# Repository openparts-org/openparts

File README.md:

# openparts

OpenParts -- an open, provenance-tracked data platform for electronic
components that generates reproducible EDA/MCAD assets from Canonical
Data instead of distributing pre-made CAD files. This repository holds
all of its code: the core libraries, validators, generators and CLI
(`crates/`), the distribution API server (`server/`), the web site
(`web/`) and the KiCad plugin (`kicad-plugin/`).

See [`docs/spec/`](docs/spec/) for the full specification set. Component
data lives in the `openparts-data` repository, checked out next to this
one (`../openparts-data`): tests, `openparts validate --data` and the
server read it from there.

## Status

First Vertical Slice (Architecture Specification section 32):
Canonical YAML -> Parser -> Validator -> Effective Model -> KiCad + STEP.
Package support covers the LQFP/TQFP, QFN, SOIC, TSSOP, SSOP, MSOP/VSSOP,
SOT, SOT-223, TO-252 (DPAK), chip (2-terminal), radial, axial, TO-92, DIP,
SIP and BGA families, castellated modules (`module`, e.g. Raspberry Pi
Pico), straight through-hole pin headers and socket strips (`header`,
`socket`; 1 or 2 rows), shrouded wire-to-board headers with an
off-centre housing (`shrouded_header`, e.g. JST XH/PH) and right-angle
pin headers (`right_angle_header`, 1 row).

3D models (STEP, STL, coloured 3MF, and an editable SolidCraft design)
are built by `openparts-solidcraft` and exported by a locally installed
[SolidCraft](https://solidcraft.io) -- see "3D models" below.

The CLI has `generate`, `validate`, `search`, `show` and `bundle` --
see "Prebuilt artifacts" below for `bundle`.

## Layout

```text
server/                  openparts-server: REST API + bundled artifacts
web/                     openparts-web: the MoonBit (rabbita) site (api/types.mbt is
                         generated from the Rust types: web/scripts/gen-api-types.sh)
kicad-plugin/            KiCad plugin (library sync GUI + launcher)
deploy/raspberry-pi/     deploy the server on a Raspberry Pi behind a Cloudflare Tunnel
crates/
├── openparts-artifacts  Part -> every artifact; the bundle manifest schema
├── openparts-core        Canonical Rust data model
├── openparts-data         YAML <-> core model
├── openparts-validator     cross-entity validation
├── openparts-client        API client for openparts-server
├── openparts-cli           command-line interface
├── pcbcad/
│   ├── openparts-pcbcad    PCB CAD-independent Symbol/Footprint IR
│   ├── openparts-kicad      KiCad adapter
│   ├── openparts-librepcb   LibrePCB adapter
│   └── openparts-pcbcraft   PCBCraft native library adapter
└── mcad/
    ├── openparts-mcad       Mechanical Geometry generators
    ├── openparts-solidcraft Mechanical Geometry -> detailed parametric
    │                        SolidCraft model, run through SolidCraft
    ├── openparts-step       STEP exporter (via openparts-solidcraft)
    └── openparts-stl        binary STL exporter (via openparts-solidcraft)
```

## Usage

```sh
cargo build --workspace
cargo test --workspace

cargo run -p openparts-cli -- validate \
  --part   ../openparts-data/parts/exemplar/ex48/EX48F100Q6.yaml \
  --device ../openparts-data/devices/exemplar/EX48F100.yaml \
  --package ../openparts-data/packages/standards/lqfp/LQFP48-7x7-P0.5.yaml \
  --source ../openparts-data/sources/exemplar/EX-DS-0001.yaml

cargo run -p openparts-cli -- generate \
  --part   ../openparts-data/parts/exemplar/ex48/EX48F100Q6.yaml \
  --device ../openparts-data/devices/exemplar/EX48F100.yaml \
  --package ../openparts-data/packages/standards/lqfp/LQFP48-7x7-P0.5.yaml \
  --source ../openparts-data/sources/exemplar/EX-DS-0001.yaml \
  --out /tmp/openparts-out
```

`generate` writes the KiCad symbol/footprint, STEP, STL, 3MF, the
SolidCraft design (`.sc`), a LibrePCB library and a generation report
for one part.

## Prebuilt artifacts

`bundle` builds every part of an `openparts-data` checkout at once, for
shipping to `openparts-server` (which then needs no SolidCraft):

```sh
cargo run --release -p openparts-cli -- bundle \
  --data ../openparts-data --out /tmp/openparts-bundle [--jobs N] [--strict]
```

Each part is validated, its Effective Model built for the base silicon
revision, and its artifacts written content-addressed (Architecture
Specification section 24) -- SolidCraft runs once per part for all 3D
formats, parts in parallel (`--jobs`, default: CPU count):

```text
<out>/
├── manifest.json
└── artifacts/sha256/<hex>     STEP, binary STL, 3MF, .sc design,
                               .kicad_sym, .kicad_mod
```

`manifest.json` (`"format": "openparts-bundle"`, `"format_version": 1`):

- `artifact_path`: `"artifacts/sha256/{sha256}"`.
- `reproducibility`: dataset git commit (and whether it was dirty),
  `schema_versions`, generator crate versions and the openparts source
  commit, `toolchain` (SolidCraft and rustc versions),
  `silicon_revision` (`null`: base), and `not_byte_reproducible`
  (`["solidcraft"]`: SolidCraft's saved design keeps build timings;
  every other kind is byte-identical across rebuilds).
- `summary`: part counts (`ok`/`partial`/`failed`), distinct artifacts,
  total bytes.
- `parts`: sorted by (manufacturer, mpn), each with `part_id`,
  `device`, `package`, `status` (`ok`, `partial`, `failed`),
  `artifacts` (kind -> `{sha256, size, content_type, filename}`; kinds
  `step`, `stl`, `3mf`, `solidcraft`, `kicad-symbol`, `kicad-footprint`)
  and `errors` (`{stage, message}`, stage one of `resolve`,
  `validation`, `effective-model`, `geometry`, `3d-model`). A part that
  fails is listed with its reason, never dropped.
- `load_errors`: dataset files that could not be parsed at all.

The manifest has no time stamp, so rebuilding from the same dataset and
toolchain reproduces it. `--strict` exits non-zero unless every part was
bundled.

## 3D models

`openparts-mcad` stays the canonical geometry (where the body and each
lead are; the footprints read the same data). `openparts-solidcraft`
turns it -- per package family and device category -- into a SolidCraft
command script with what the real part looks like: drafted mold bodies,
formed gull-wing and through-hole leads, plated end caps, inlaid QFN
terminals, polarity bands and stripes, can sleeves, LED lenses, ...
Shared dimensions are SolidCraft design parameters (`body_w`, `pitch`,
`leads_per_side`, `lead_t`, ...) referenced by expressions, so the `.sc`
design `generate` writes can be edited in SolidCraft and rebuilds
consistently.

The shapes are YAML templates in
`crates/mcad/openparts-solidcraft/templates/` -- SolidCraft command
lists with `{{var}}` placeholders, one per building block (a gull-wing
lead row, a molded body, an MLCC, an electrolytic can, ...). The Rust
side only decides which templates to use and fills their variables from
the geometry; runs use SolidCraft's `--param-check strict`, so a
misspelt command parameter fails loudly.

SolidCraft must be installed: the Flatpak `io.tangencylabs.solidcraft`,
or `solidcraft-cli` on `PATH`; `OPENPARTS_SOLIDCRAFT_CLI` (a binary
path) or `OPENPARTS_SOLIDCRAFT_FLATPAK` (an app id) override the choice.
Tests that need it skip themselves when it is missing.

To review every model in the dataset (writes a script, STEP and PNG per
package):

```sh
cargo run -p openparts-solidcraft --example gallery -- ../openparts-data /tmp/gallery [filter]
```

`search`/`show` talk to an `openparts-server` instance (optional --
every other subcommand works entirely offline against local
`openparts-data` files). Point them at one with `--registry` or the
`OPENPARTS_REGISTRY_URL` env var (default `http://127.0.0.1:8080`):

```sh
# in a separate terminal, from openparts-server/ (OPENPARTS_ARTIFACT_DIR
# is optional: a `bundle` output to serve 3D models from):
OPENPARTS_DATA_DIR=../openparts-data OPENPARTS_ARTIFACT_DIR=/tmp/openparts-bundle \
  cargo run --release

# then:
cargo run -p openparts-cli -- search RP2040
cargo run -p openparts-cli -- show raspberrypi RP2040
```

## License

| What | License |
|---|---|
| This repository's code | [MIT](LICENSE-MIT) OR [Apache-2.0](LICENSE-APACHE), at your option |
| The part data ([openparts-data](https://github.com/openparts-org/openparts-data)) | [CC-BY-4.0](https://creativecommons.org/licenses/by/4.0/) |
| Generated artifacts (symbols, footprints, 3D models, KiCad/LibrePCB/PCBCraft libraries) | [CC0-1.0](LICENSES/CC0-1.0.txt): use them in any design or product without conditions |

Values are facts read from manufacturers' datasheets; no datasheet text,
drawings or vendor CAD geometry is copied (Architecture Specification
section 30).

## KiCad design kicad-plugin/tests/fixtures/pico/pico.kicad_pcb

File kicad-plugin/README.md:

# openparts-kicad-plugin

A small native GUI companion app for [OpenParts](https://github.com/openparts-org/openparts),
with three tabs:

- **Search**: the registry's faceted catalog (`GET /v1/catalog`): text, the category tree,
  manufacturer, package family, size code, pins, pitch, mounting, the package structure (rows,
  gender, orientation, shroud, exposed pad), review state, body size ranges and the electrical
  parameter facets (values and min/max ranges such as `10n`..`1u`). The results table's columns
  follow the results: a capacitor search shows size, capacitance, voltage, dielectric; a
  connector search rows, gender, pitch. Pick a part and **Install into project**.
- **BOM check**: the open project's BOM against the registry (`POST /v1/bom/check`), with each
  line's status, issues and match. Select a line to see its candidates (the match, the listed
  alternatives, or **Find alternatives**: `GET .../alternatives`), each with **Install** and
  **Use MPN**.
- **Footprints**: every OpenParts footprint of the project (on its `.kicad_pcb` boards and in its
  project footprint libraries) whose `OpenParts placement` hash differs from the registry's
  current Placement Model (`GET .../placement`, see `docs/spec/placement-model.md` section 13).
  **Update** reinstalls the library footprint; board copies are then updated in KiCad with
  Tools > Update Footprints from Library.

It does **not** place anything on the schematic or board -- once a part is installed, pick it up
from KiCad's normal Symbol/Footprint picker as usual.

### Install into project

Installing (the same path as `openparts kicad-install`):

- downloads the part's KiCad symbol, KiCad footprint, and STEP artifacts (via
  `openparts-client`, which verifies each download's SHA-256 content hash before trusting it),
- writes the STEP file under `<project>/openparts_3d/<MPN>.step`,
- writes/merges the footprint into `<project>/openparts.pretty/<MPN>.kicad_mod`, patching its
  `(model ...)` block to point at the downloaded STEP file so the 3D viewer works immediately,
- merges the symbol into `<project>/openparts.kicad_sym` (creating it if needed, replacing an
  existing entry with the same name if reinstalling),
- registers both libraries in the project's `sym-lib-table`/`fp-lib-table` if not already
  present.

All of this is idempotent: installing the same part twice updates the existing entries in place
rather than duplicating them.

### How the BOM is read

The root schematic is `<name>.kicad_sch` of the project's `.kicad_pro`. The app walks the sheet
hierarchy (`Sheetfile`), reads every placed symbol's Reference (per sheet instance), Value,
Footprint, MPN (`MPN`, `Manufacturer Part Number`, ...), Manufacturer and DNP fields, skips power
symbols and `in_bom no`, merges the units of multi-unit symbols, and groups identical lines into a
KiCad-style BOM CSV. With the source set to "kicad-cli / schematic" and `kicad-cli` on `PATH` (or
`KICAD_CLI`), kicad-cli's netlist is sent instead; the symbol locations still come from the
schematic.

**Use MPN** writes the MPN (and the manufacturer, where the symbol has that field) into the
symbols' existing MPN field, rewriting only that string in the `.kicad_sch`. It does so only when
every symbol of the line has an MPN field on every unit and sits on a sheet used once; otherwise
it copies the MPN to the clipboard and says why. Reload an open schematic afterwards
(File > Revert).

### Command line

`openparts kicad-check-stale <project>` is the Footprints tab's check (`--all`, `--json`,
`--strict`).

> **Verified end-to-end** on a real Windows machine with KiCad 10: `install.ps1` downloading and
> installing the binary + launcher, the "OpenParts" toolbar button in the PCB editor, searching,
> installing RP2040, the symbol/footprint libraries being correctly registered as project-specific
> libraries, and the footprint being placed on a real board.
>
> One thing to know: after installing a part for the first time in a KiCad session, **restart the
> Symbol Editor / Footprint Editor / 3D viewer windows** (close and reopen) before the new
> `openparts` library shows up in them. KiCad reads library tables once when each of those windows
> opens and doesn't hot-reload them if the underlying `sym-lib-table`/`fp-lib-table` changes while
> they're already open -- this is KiCad's own behavior, not something this tool can avoid.

## Quick install

Downloads a prebuilt binary and registers the [KiCad toolbar launcher](#launching-from-inside-kicad)
for you -- no Rust toolchain needed.

**Linux:**
```sh
curl -fsSL https://raw.githubusercontent.com/openparts-org/openparts/main/kicad-plugin/install.sh | bash
```

**Windows (PowerShell):**
```powershell
irm https://raw.githubusercontent.com/openparts-org/openparts/main/kicad-plugin/install.ps1 | iex
```
Both scripts try to auto-detect your KiCad plugin directory; if they can't, they'll tell you how to
find it via KiCad's own Tools > External Plugins > Open Plugin Directory and re-run with an explicit
path (`-PluginDir` on Windows, `--plugin-dir` on Linux). Afterwards, restart KiCad (or Tools >
External Plugins > Refresh Plugins) and look for the new "OpenParts" button in the PCB editor
toolbar -- **not** in the Plugin and Content Manager's own "Installed" list, which only tracks
packages it installed itself and never shows an unpackaged Action Plugin like this one.

macOS isn't built by CI yet -- see [Manual install / building from source](#manual-install--building-from-source).

## Manual install / building from source

```sh
cargo build --release
```

This repo depends on `openparts-client`/`openparts-core` from a sibling checkout of
[`openparts`](https://github.com/openparts-org/openparts) via relative path
(`../openparts/crates/...`) -- clone both repos next to each other:

```
OpenParts/
├── openparts/
└── openparts-kicad-plugin/
```

## Running

```sh
cargo run --release
```

Enter your `openparts-server` URL (defaults to `$OPENPARTS_REGISTRY_URL`, else
`http://localhost:8080`) and the project directory. The project directory can also be pre-filled
via `--project-dir <path>` on the command line, which is how the KiCad launcher below invokes it.

## Launching from inside KiCad

`kicad-integration/openparts_launcher.py` is a pcbnew Action Plugin: it adds an "OpenParts" button
to the PCB Editor's toolbar that runs this app as an external process with `--project-dir` already
set to the currently open project's directory. It does not use KiCad's IPC API (which has no
library-management support to begin with) -- it's the same "Python toolbar button that shells out
to an external tool" pattern used by plugins like InteractiveHtmlBom.

The [Quick install](#quick-install) scripts set this up automatically, including writing a config
file the launcher reads to find the binary. If you're building from source instead, install it
manually:

```sh
mkdir -p ~/.local/share/kicad/9.0/scripting/plugins
ln -s "$(pwd)/kicad-integration/openparts_launcher.py" \
    ~/.local/share/kicad/9.0/scripting/plugins/openparts_launcher.py
```

Adjust `9.0` to your installed KiCad version (Help > About KiCad; Tools > External Plugins > Open
Plugin Directory is the authoritative way to find this folder on any OS/version), then restart
KiCad or use Tools > External Plugins > Refresh Plugins. The launcher looks for the binary in this
order: the `OPENPARTS_KICAD_PLUGIN_BIN` environment variable, then the installer's config file
(`~/.config/openparts-kicad-plugin/binary_path.txt`, or `%APPDATA%\openparts-kicad-plugin\binary_path.txt`
on Windows), then the `DEFAULT_BINARY_PATH` constant at the top of the script -- edit that constant
if your manual checkout lives somewhere else and you don't want to set an environment variable or
config file.

## Project-path auto-detect (alternative to the launcher above)

Optional feature `kicad-ipc`, off by default:

```sh
cargo build --features kicad-ipc
```

When enabled, the "Detect via KiCad" button uses [`kicad-ipc-rs`](https://docs.rs/kicad-ipc-rs) to
ask a running KiCad instance (10.0.1+, with its IPC API enabled in Preferences) for its current
project path. This is best-effort and never required -- the project directory can always be typed
in by hand, or pre-filled via the launcher plugin above (which needs neither this feature nor
`cmake`). It's off by default because `kicad-ipc-rs` pulls in `nng-sys`, which compiles the `nng`
C library from source via `cmake`; that's a real system dependency not everyone building this app
needs.

## Testing

```sh
cargo test
```

Everything but drawing is tested offline: the search state and its columns (`src/search.rs`),
schematic reading, BOM grouping and MPN writing against a trimmed copy of a Raspberry Pi Pico
board (`tests/fixtures/pico`, `src/schematic.rs`, `src/bom.rs`), the stale scan
(`src/stale.rs`, `openparts-client`'s `kicad_stale`), and installing from a pre-filled client
cache (`src/install.rs`). `src/ui.rs` only draws. With a server running,
`OPENPARTS_TEST_REGISTRY=http://127.0.0.1:8080 cargo test -- --ignored --nocapture` checks the
fixture's BOM against it.

`src/kicad_detect.rs`'s real IPC path (behind the `kicad-ipc` feature) could not be exercised in
the environment this was developed in (no `cmake` available to build `nng-sys`, no running KiCad
instance). Its two API calls (`KiCadClientBlocking::connect()`, `.get_current_project_path()`) are
copied verbatim from `kicad-ipc-rs`'s own documented usage, not guessed -- but this path has only
been verified inside real KiCad by the OpenParts maintainer, not by an automated test here.

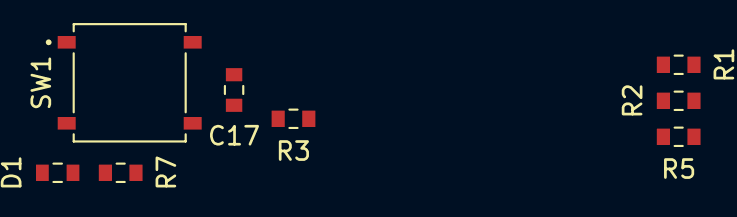
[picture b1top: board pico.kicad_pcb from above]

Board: 0 copper layers, 8 parts (0 on the bottom side), 4 nets, no tracks yet.

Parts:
C17: CL10C150JB8NNNC
D1: APT1608SGC
R1, R2: RC0603FR-0727RL
R3: RC0603FR-071KL
R5: RC0603FR-075K1L
R7: RC0603FR-07330RL
SW1: B3FS-1050

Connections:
BOOTSEL: SW1.1, SW1.2
GND: C17.2, D1.1, R5.2, SW1.3, SW1.4
LED_A: D1.2, R7.2
XTAL_OUT: C17.1, R3.2
